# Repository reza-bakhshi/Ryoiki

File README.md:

# Ryoiki

⚠️ **THIS PROJECT IS UNDER ACTIVE DEVELOPMENT AND TESTING
DO NOT MANUFACTURE OR USE THE HARDWARE WITHOUT YOUR OWN VERIFICATION**

---

## Images

### TOP

### BOTTOM

---

## Overview

**Ryoiki** is an RP2040-based multi-purpose USB protocol bridge designed for embedded development workflows where USB ports are limited and multiple hardware interfaces are required.

This project is inspired by:

* BlueTag
* Bus Pirate
* pico-uart-bridge

The device is designed to:

* Bridge multiple protocols (UART / I²C / SPI → USB)
* Reduce the number of USB ports used
* Act as a compact RP2040 header-style board with limited pins when needed

---

## Project Goal

During embedded Linux development, using multiple USB-to-serial converters quickly consumes all available USB ports and creates cable clutter.

**Ryoiki** solves this by providing multiple interfaces over a single USB connection in a compact and flexible form factor.

---

## Current Status

| Interface | Status                                 |
| --------- | -------------------------------------- |
| UART      | ✅ Working                              |
| I²C       | 🚧 In development (currently disabled) |
| SPI       | 🚧 In development (currently disabled) |

This is a prototype and both hardware and firmware are still under validation.

---

## Firmware

The current firmware is based on my fork of the pico-uart-bridge project.

When connected to a Linux system, the device enumerates as two independent CDC interfaces:

```text
/dev/ttyACM0  
/dev/ttyACM1
```

Each interface provides access to one UART channel.

### Features

* Auto-baudrate detection
* No manual baudrate configuration required
* Plug-and-play on Linux

---

## Hardware Design

The hardware is designed based on:

* RP2040 Zero form factor
* Official Raspberry Pi RP2040 hardware design guidelines

### Design Targets

* Compact size
* Low component count
* High flexibility for future features
* Header-style usability in external projects

### Hardware Features

* RP2040 microcontroller
* USB device interface
* Dual UART ports
* Dedicated **RX/TX status LEDs** for each UART

Designed with **KiCad**.

---

## Use Cases

* Embedded Linux development
* Multi-device serial debugging
* Compact USB lab tool
* Future multi-protocol debugging interface

---

## Future Plans

| Feature                   | Description                                   | Status            |
| ------------------------- | --------------------------------------------- | ----------------- |
| I²C Bridge                | USB to I²C interface                          | 🚧 In development |
| SPI Bridge                | USB to SPI interface                          | 🚧 In development |
| Multi-protocol Debug Mode | Bus Pirate / BlueTag-like functionality       | 🧩 Planned        |

---

## Development Notes

* Hardware revisions are expected
* Firmware is evolving rapidly
* Not production-ready

---

## Repository Structure

```text
/hardware   → KiCad design files  
/firmware   → RP2040 firmware  
/docs       → Documentation  
```

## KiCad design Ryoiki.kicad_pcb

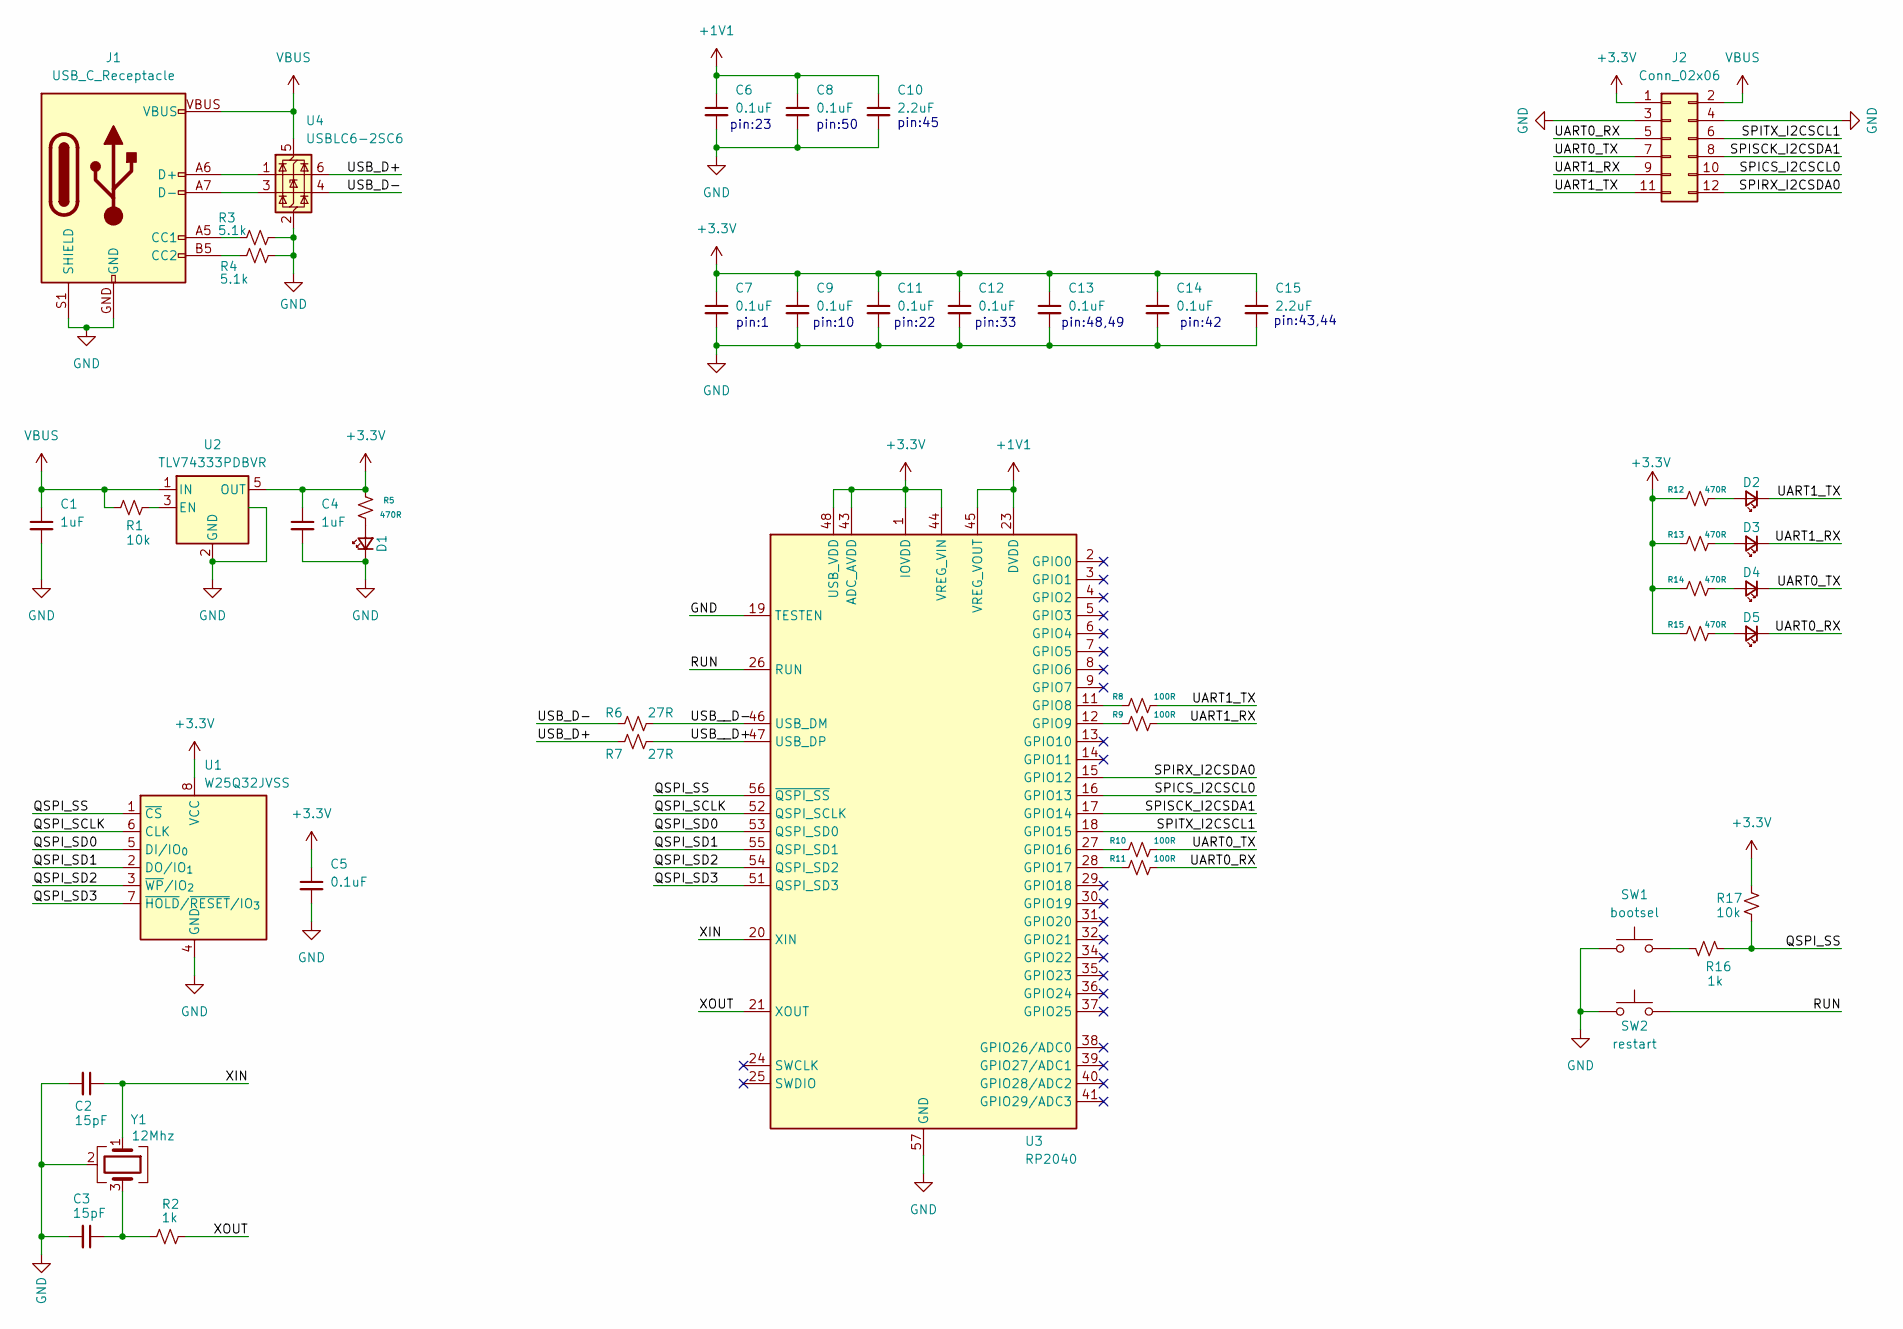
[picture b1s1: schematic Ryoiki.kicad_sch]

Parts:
C1, C4: 1uF; C_0402_1005Metric_Pad0.74x0.62mm_HandSolder; Voltage 25V
C2, C3: 15pF; C_0402_1005Metric_Pad0.74x0.62mm_HandSolder
C5, C6, C7, C8, C9, C11, C12, C13, C14: 0.1uF; C_0402_1005Metric_Pad0.74x0.62mm_HandSolder; Voltage 25V
C10, C15: 2.2uF; C_0402_1005Metric_Pad0.74x0.62mm_HandSolder; Voltage 25V
D1: PWR; LED_0402_1005Metric_Pad0.77x0.64mm_HandSolder
D2: TX2; LED_0402_1005Metric_Pad0.77x0.64mm_HandSolder
D3: RX2; LED_0402_1005Metric_Pad0.77x0.64mm_HandSolder
D4: TX1; LED_0402_1005Metric_Pad0.77x0.64mm_HandSolder
D5: RX1; LED_0402_1005Metric_Pad0.77x0.64mm_HandSolder
J1: USB_C_Receptacle; USB-C_16
J2: Conn_02x06; PinHeader_2x06_SMD_P2.54mm_Horizontal
R1, R17: 10k; R_0402_1005Metric_Pad0.72x0.64mm_HandSolder
R2, R16: 1k; R_0402_1005Metric_Pad0.72x0.64mm_HandSolder
R3, R4: 5.1k; R_0402_1005Metric_Pad0.72x0.64mm_HandSolder
R5, R12, R13, R14, R15: 470R; R_0402_1005Metric_Pad0.72x0.64mm_HandSolder
R6, R7: 27R; R_0402_1005Metric_Pad0.72x0.64mm_HandSolder
R8, R9, R10, R11: 100R; R_0402_1005Metric_Pad0.72x0.64mm_HandSolder
SW1: bootsel; SW_SPST_CK_RS282G05A3
SW2: restart; SW_SPST_CK_RS282G05A3
U1: W25Q32JVSS; SOIC-8_5.3x5.3mm_P1.27mm
U2: TLV74333PDBVR; SOT-23-5
U3: RP2040; QFN-56-1EP_7x7mm_P0.4mm_EP3.2x3.2mm
U4: USBLC6-2SC6; SOT-23-6
Y1: 12Mhz; Crystal_SMD_4Pin

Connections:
+1V1: C6.1, C8.1, C10.1, U3.23 (DVDD), U3.45 (VREG_VOUT), U3.50 (DVDD)
+3.3V: C4.1, C5.1, C7.1, C9.1, C11.1, C12.1, C13.1, C14.1, C15.1, J2.1, R5.1, R12.1, R13.1, R14.1, R15.1, R17.1, U1.8 (VCC), U2.5 (OUT), U3.1 (IOVDD), U3.10 (IOVDD), U3.22 (IOVDD), U3.33 (IOVDD), U3.42 (IOVDD), U3.43 (ADC_AVDD), U3.44 (VREG_VIN), U3.48 (USB_VDD), U3.49 (IOVDD)
/QSPI_SCLK: U1.6 (CLK), U3.52 (QSPI_SCLK)
/QSPI_SD0: U1.5 (DI/IO_{0}), U3.53 (QSPI_SD0)
/QSPI_SD1: U1.2 (DO/IO_{1}), U3.55 (QSPI_SD1)
/QSPI_SD2: U1.3 (~WP/IO_{2}), U3.54 (QSPI_SD2)
/QSPI_SD3: U1.7 (~HOLD/~RESET/IO_{3}), U3.51 (QSPI_SD3)
/QSPI_SS: R16.2, R17.2, U1.1 (~CS), U3.56 (~QSPI_SS)
/RUN: SW2.2, U3.26 (RUN)
/SPICS_I2CSCL0: J2.10, U3.16 (GPIO13)
/SPIRX_I2CSDA0: J2.12, U3.15 (GPIO12)
/SPISCK_I2CSDA1: J2.8, U3.17 (GPIO14)
/SPITX_I2CSCL1: J2.6, U3.18 (GPIO15)
/UART0_RX: D5.1 (K), J2.5, R11.2
/UART0_TX: D4.1 (K), J2.7, R10.2
/UART1_RX: D3.1 (K), J2.9, R9.2
/UART1_TX: D2.1 (K), J2.11, R8.2
/USB_D+: R7.1, U4.6 (I/O1)
/USB_D-: R6.1, U4.4 (I/O2)
/USB__D+: R7.2, U3.47 (USB_DP)
/USB__D-: R6.2, U3.46 (USB_DM)
/XIN: C2.1, U3.20 (XIN), Y1.1
/XOUT: R2.2, U3.21 (XOUT)
GND: C1.2, C2.2, C3.2, C4.2, C5.2, C6.2, C7.2, C8.2, C9.2, C10.2, C11.2, C12.2, C13.2, C14.2, C15.2, D1.1 (K), J1.GND, J1.S1 (SHIELD), J1.S2 (SHIELD), J1.S3 (SHIELD), J1.S4 (SHIELD), J2.3, J2.4, R3.2, R4.2, SW1.1, SW2.1, U1.4 (GND), U2.2 (GND), U2.4 (NC), U3.19 (TESTEN), U3.57 (GND), U4.2 (GND), Y1.2 (G), Y1.4 (G)
unnamed: C3.1, R2.1, Y1.3
unnamed: D1.2 (A), R5.2
unnamed: D2.2 (A), R12.2
unnamed: D3.2 (A), R13.2
unnamed: D4.2 (A), R14.2
unnamed: D5.2 (A), R15.2
unnamed: J1.A5 (CC1), R3.1
unnamed: J1.B5 (CC2), R4.1
unnamed: J1.A6 (D+), J1.B6 (D+), U4.1 (I/O1)
unnamed: J1.A7 (D-), J1.B7 (D-), U4.3 (I/O2)
unnamed: R16.1, SW1.2
unnamed: R1.1, U2.3 (EN)
unnamed: R8.1, U3.11 (GPIO8)
unnamed: R9.1, U3.12 (GPIO9)
unnamed: R10.1, U3.27 (GPIO16)
unnamed: R11.1, U3.28 (GPIO17)
VBUS: C1.1, J1.VBUS, J2.2, R1.2, U2.1 (IN), U4.5 (VBUS)

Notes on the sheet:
pin:42
pin:1
pin:23
pin:45
pin:50
pin:22
pin:48,49
pin:33
pin:43,44
pin:10

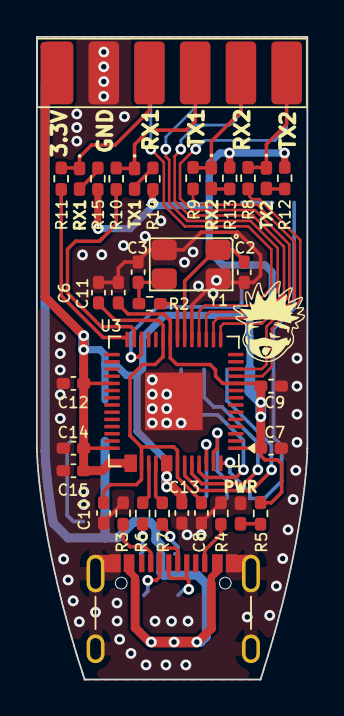
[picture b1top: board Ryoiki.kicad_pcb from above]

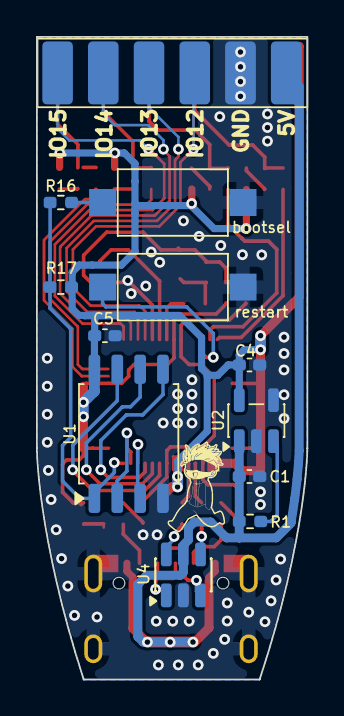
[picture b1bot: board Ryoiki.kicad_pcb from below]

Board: 2 copper layers, 15.0 x 35.7 mm, 46 parts (11 on the bottom side), 41 nets.

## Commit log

2026-02-20 Ryoiki Tenkai 🤞 - initial commit [V1.0]
2026-02-21 update README.md file
2026-02-23 - Added ESD protection (USBLC6-2SC6) to the USB data lines and VBUS. - add more satoru gojo
2026-04-11 update readme file
2026-04-11 update gojo icons
2026-04-14 update from kicad v9 to v10
2026-04-14 update readme.md file : add new images
